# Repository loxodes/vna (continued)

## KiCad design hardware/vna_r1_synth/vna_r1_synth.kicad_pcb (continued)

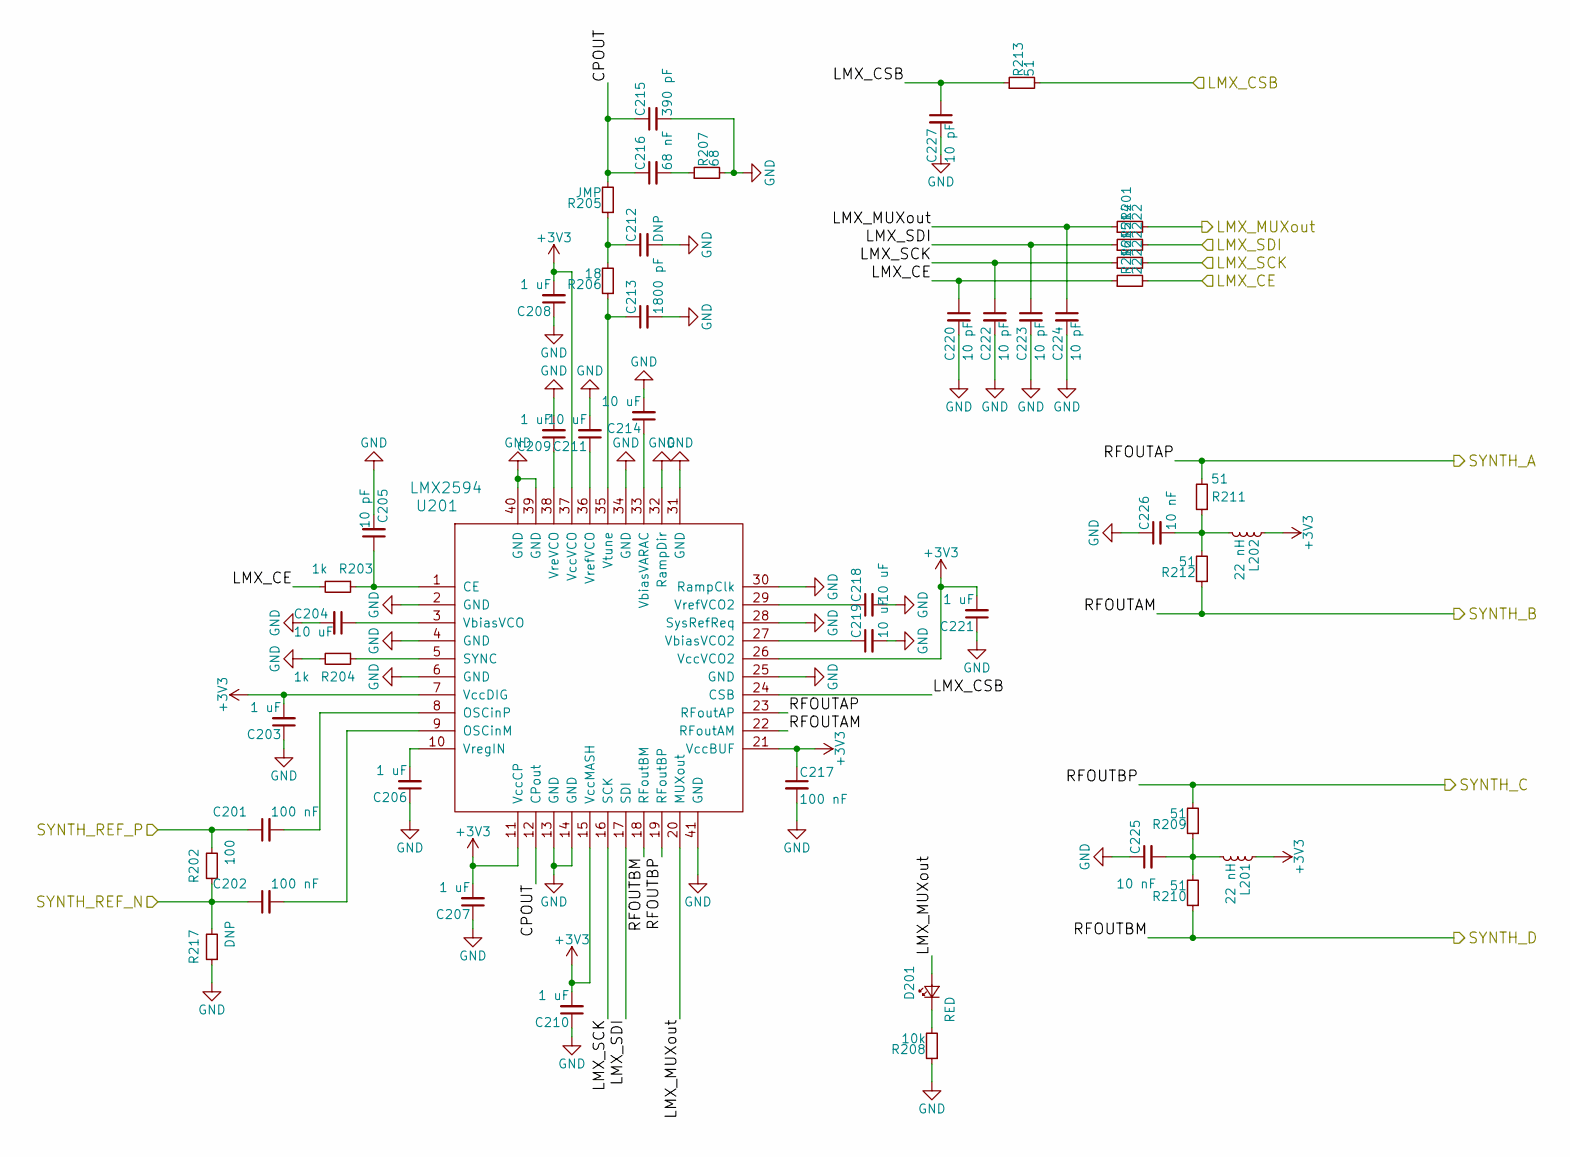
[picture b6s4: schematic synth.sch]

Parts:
C201, C202, C217: 100 nF; C_0402
C203, C206, C207, C208, C209, C210, C221: 1 uF; C_0402
C204, C211, C214, C218, C219: 10 uF; C_0603
C205, C220, C222, C223, C224, C227: 10 pF; C_0603
C212: DNP; C_0402
C213: 1800 pF; C_0402
C215: 390 pF; C_0402
C216: 68 nF; C_0402
C225, C226: 10 nF; C_0402
D201: RED; LED_0603
L201, L202: 22 nH; R_0402
R201, R214, R215, R216: 22; R_0402
R202: 100; R_0402
R203, R204: 1k; R_0402
R205: JMP; R_0402
R206: 18; R_0402
R207: 68; R_0402
R208: 10k; R_0402
R209, R210, R211, R212, R213: 51; R_0402
R217: DNP; R_0402
U201: LMX2594; QFN-40-1EP_6x6mm_Pitch0.5mm

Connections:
+3V3: C203.2, C207.2, C208.2, C210.2, C217.1, C221.2, L201.1, L202.1, U201.7 (VccDIG), U201.11 (VccCP), U201.15 (VccMASH), U201.21 (VccBUF), U201.26 (VccVCO2), U201.37 (VccVCO); also elsewhere on the board
/AUX_OUT: R209.2, U201.19 (RFoutBP); also elsewhere on the board
/LO_PORT1: R212.1, U201.22 (RFoutAM); also elsewhere on the board
/LO_PORT2: R210.1, U201.18 (RFoutBM); also elsewhere on the board
/RF_PORT: R211.2, U201.23 (RFoutAP); also elsewhere on the board
/SPI_SCK: R215.2; also elsewhere on the board
/SPI_SDI: R214.2; also elsewhere on the board
/conn_power/LMX_CE: R216.2; also elsewhere on the board
/conn_power/LMX_CS: R213.2; also elsewhere on the board
/conn_power/LMX_LCK: R201.2; also elsewhere on the board
/conn_power/SYNTH_REF_N: C202.1, R202.1, R217.2; also elsewhere on the board
/conn_power/SYNTH_REF_P: C201.1, R202.2; also elsewhere on the board
/synth/CE: C220.1, R203.2, R216.1
/synth/CPOUT: C215.1, C216.1, R205.2, U201.12 (CPout)
/synth/CSB: C227.1, R213.1, U201.24 (CSB)
/synth/MUXout: C224.1, D201.2 (A), R201.1, U201.20 (MUXout)
/synth/SCK: C222.1, R215.1, U201.16 (SCK)
/synth/SDI: C223.1, R214.1, U201.17 (SDI)
GND: C203.1, C204.2, C205.2, C206.1, C207.1, C208.1, C209.2, C210.1, C211.2, C212.2, C213.2, C214.2, C215.2, C217.2, C218.2, C219.2, C220.2, C221.1, C222.2, C223.2, C224.2, C225.1, C226.1, C227.2, R204.2, R207.2, R208.1, R217.1, U201.2 (GND), U201.4 (GND), U201.6 (GND), U201.13 (GND), U201.14 (GND), U201.25 (GND), U201.28 (SysRefReq), U201.30 (RampClk), U201.31 (GND), U201.32 (RampDir), U201.34 (GND), U201.39 (GND), U201.40 (GND), U201.41 (GND); also elsewhere on the board
unnamed: C201.2, U201.8 (OSCinP)
unnamed: C202.2, U201.9 (OSCinM)
unnamed: C204.1, U201.3 (VbiasVCO)
unnamed: C205.1, R203.1, U201.1 (CE)
unnamed: C206.2, U201.10 (VregIN)
unnamed: C209.1, U201.38 (VreVCO)
unnamed: C211.1, U201.36 (VrefVCO)
unnamed: C212.1, R205.1, R206.2
unnamed: C213.1, R206.1, U201.35 (Vtune)
unnamed: C214.1, U201.33 (VbiasVARAC)
unnamed: C216.2, R207.1
unnamed: C218.1, U201.29 (VrefVCO2)
unnamed: C219.1, U201.27 (VbiasVCO2)
unnamed: C225.2, L201.2, R209.1, R210.2
unnamed: C226.2, L202.2, R211.1, R212.2
unnamed: D201.1 (K), R208.2
unnamed: R204.1, U201.5 (SYNC)

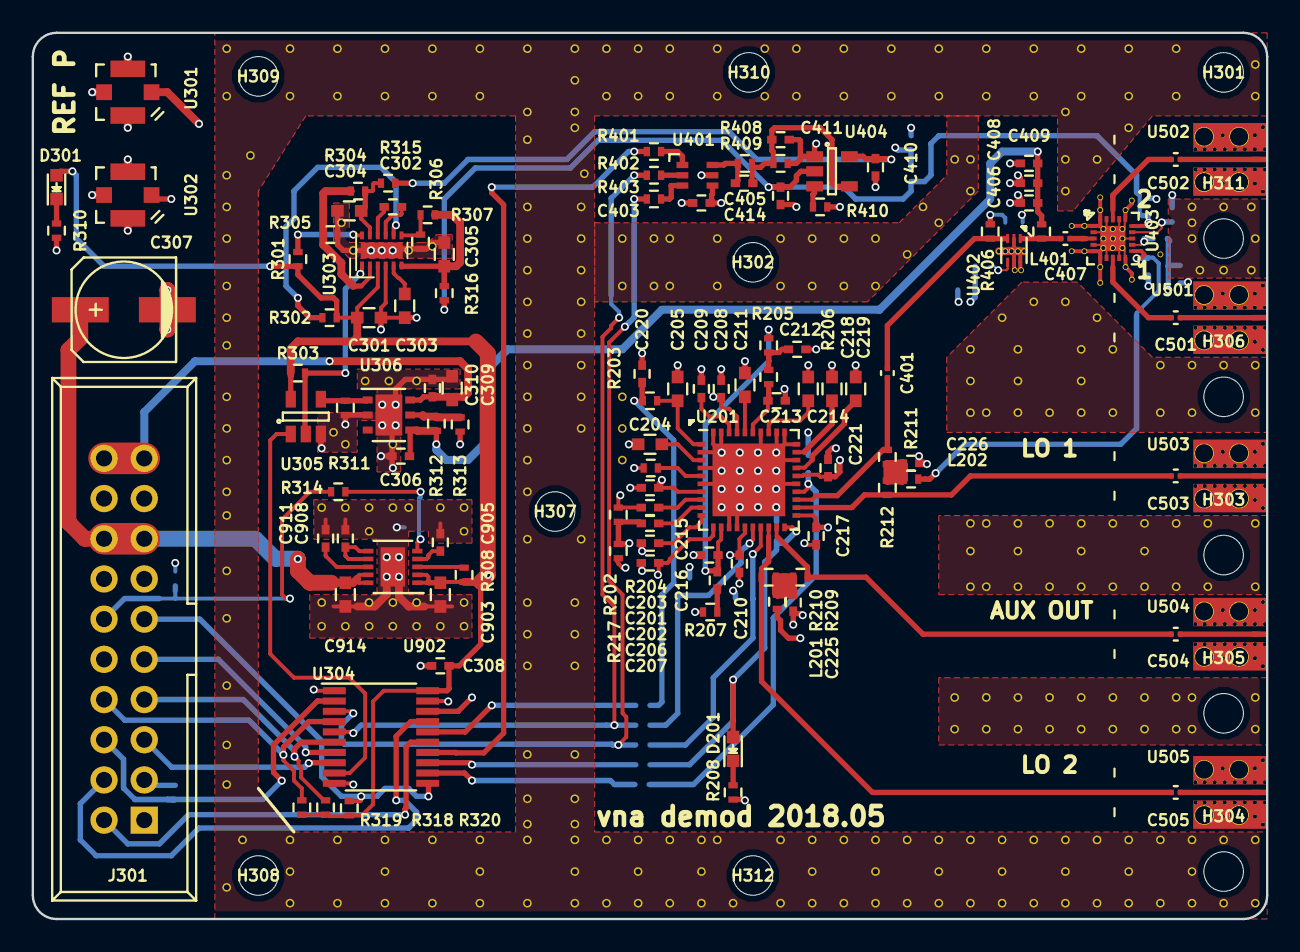
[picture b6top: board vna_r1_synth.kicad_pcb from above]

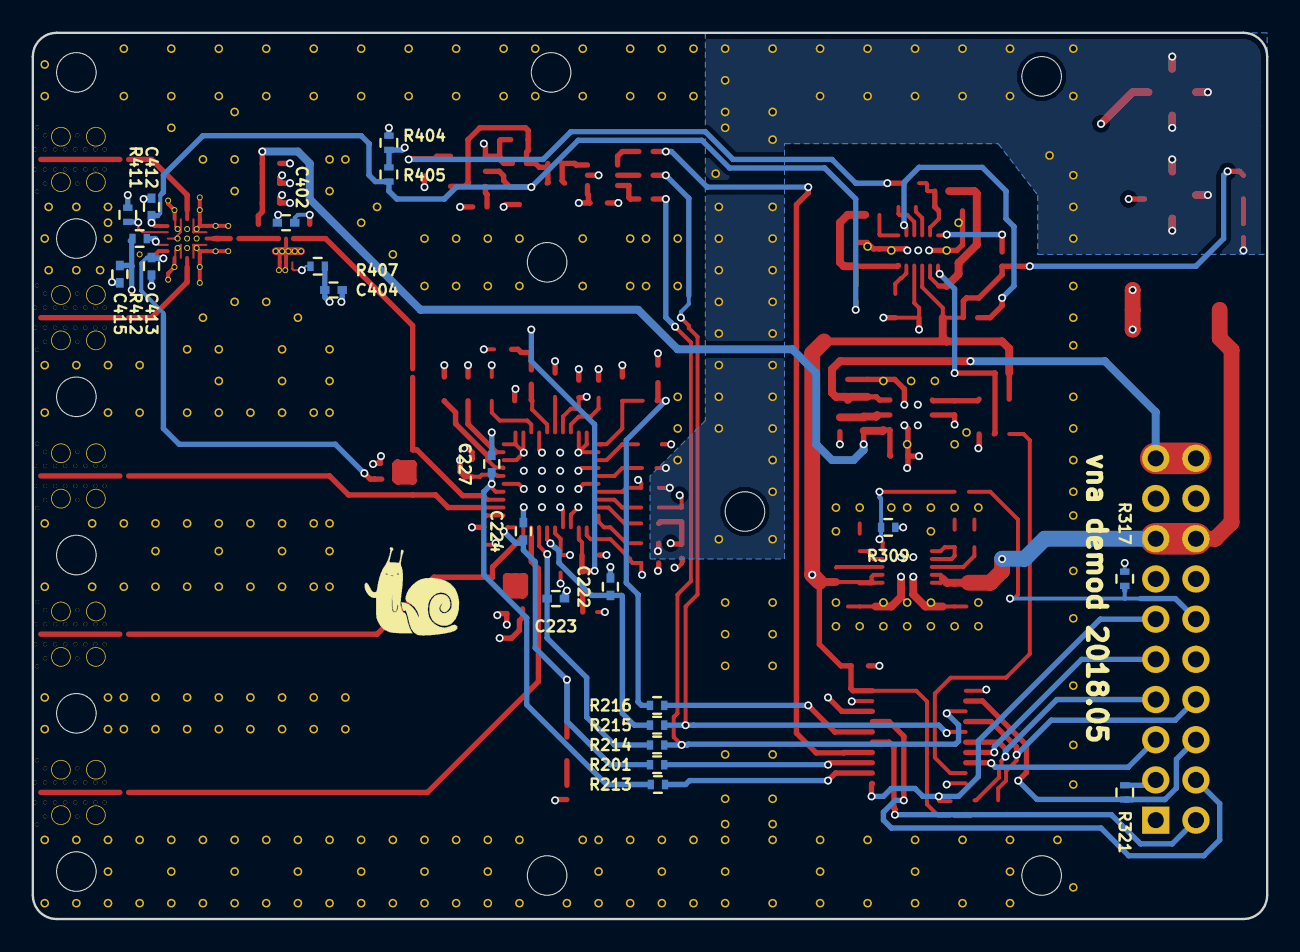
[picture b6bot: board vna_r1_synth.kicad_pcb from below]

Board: 4 copper layers, 78.0 x 56.0 mm, 147 parts (22 on the bottom side), 92 nets.
